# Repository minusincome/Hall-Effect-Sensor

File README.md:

# Hall Effect Sensor

This device is a purely electrical design of a Hall Effect Sensor that measures the magnitude of the magnetic field and displays it on a voltmeter display. 

## Installation

The PCB design files are made in KiCAD which is an open source program and can be downloaded on [their website](http://www.kicad-pcb.org/). 

## Components

The PCB design rules are made to comply with the requirements by [Eurocircuits](https://www.eurocircuits.com/standard-pool-your-default-choice-for-your-pcb/).

 - Hall effect sensor (SS496A1)
 - LCD display (SP200)
 - Differential Amplifier (LTC2053CMS8#PBF)
 - LDO Voltage Regulator (MCP1703AT-5002E/CB)
 - S1P1 Switch
 - 9V Battery and Battery Holder
 
## Contributing

Pull requests are welcome.

## License
[MIT](https://choosealicense.com/licenses/mit/)

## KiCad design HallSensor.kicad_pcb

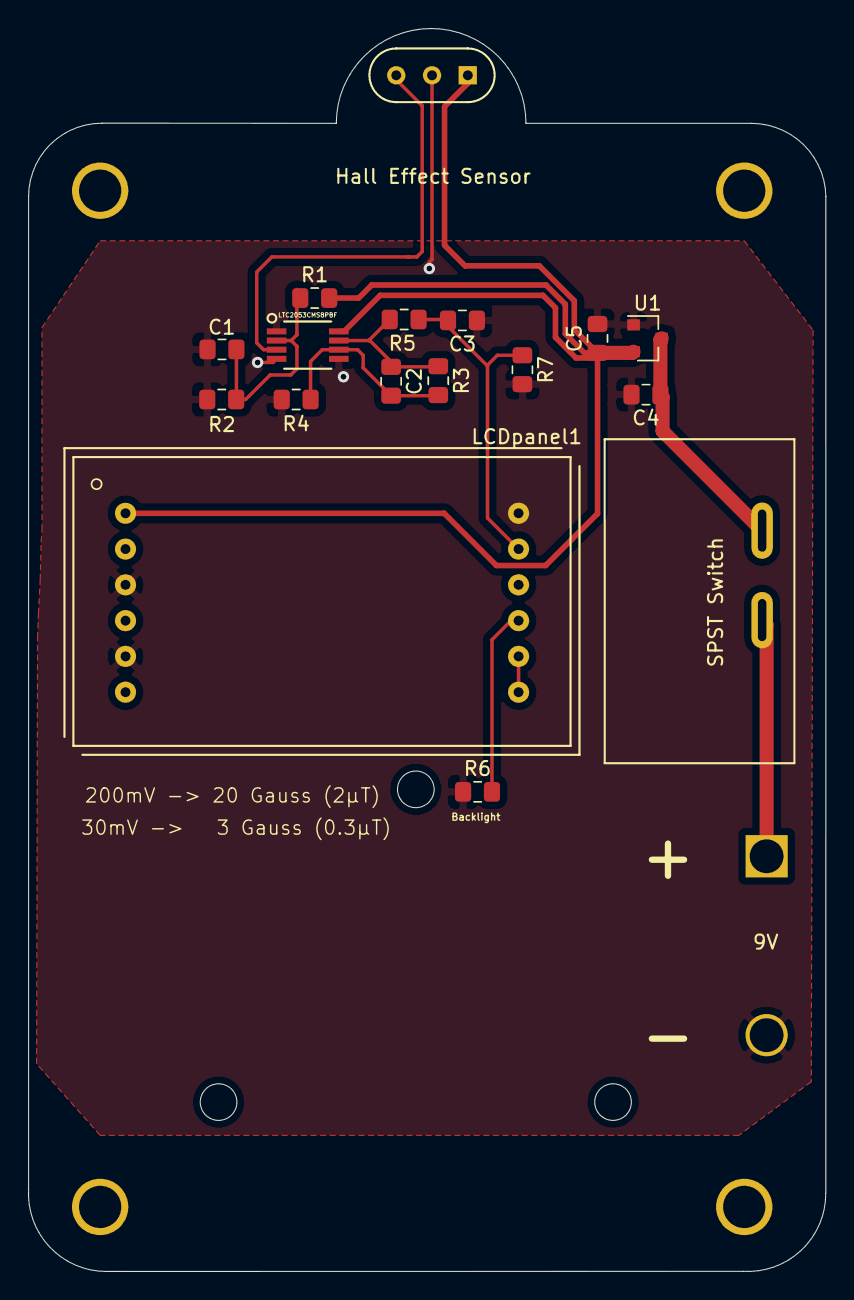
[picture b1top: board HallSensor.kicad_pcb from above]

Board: 2 copper layers, 56.6 x 88.2 mm, 18 parts (1 on the bottom side), 11 nets.

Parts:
BT1: Battery_Cell; BatteryHolder_Eagle_12BH611-GR
C1, C2, C3, C4, C5: 0.1uF; C_0805_2012Metric_Pad1.15x1.40mm_HandSolder
DifferentialAmp,Gain=4: LTC2053CMS8PBF; MSOP-8_MS
Hall Effect Sensor: SS495A; SIP3_11.6x8.5mm
LCDpanel1: CC56-12CGKWA; Display - SP200
R1, R2, R4: 10kΩ; R_0805_2012Metric_Pad1.15x1.40mm_HandSolder
R3: 30kΩ; R_0805_2012Metric_Pad1.15x1.40mm_HandSolder
R5, R6: R; R_0805_2012Metric_Pad1.15x1.40mm_HandSolder
R7: 10kO; R_0805_2012Metric_Pad1.15x1.40mm_HandSolder
SPST Switch: SW_SPST; SwitchONOFF
U1: MCP1703A-5002_SOT23; SOT-23

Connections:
+5V: C5.1, DifferentialAmp,Gain=4.8, Hall Effect Sensor.1, LCDpanel1.1, R1.2, U1.2
GND: BT1.2, C1.2, C3.2, C4.2, C5.2, DifferentialAmp,Gain=4.1, DifferentialAmp,Gain=4.4, DifferentialAmp,Gain=4.5, Hall Effect Sensor.2, LCDpanel1.3, LCDpanel1.5, LCDpanel1.12, R2.2, R4.2, R6.1, R7.2, U1.1
unnamed: BT1.1, SPST Switch.1
unnamed: C1.1, DifferentialAmp,Gain=4.2, R1.1, R2.1
unnamed: C2.1, DifferentialAmp,Gain=4.7, R3.1, R5.2
unnamed: C2.2, DifferentialAmp,Gain=4.6, R3.2, R4.1
unnamed: C3.1, LCDpanel1.11, R5.1, R7.1
unnamed: C4.1, SPST Switch.2, U1.3
unnamed: DifferentialAmp,Gain=4.3, Hall Effect Sensor.3
unnamed: LCDpanel1.7, LCDpanel1.8
unnamed: LCDpanel1.9, R6.2

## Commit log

2019-07-03 PCB design and library files
2019-07-03 Image of the final product
2019-07-03 Resizing final product image
